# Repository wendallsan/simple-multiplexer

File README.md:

# SynthUx Academy Simple Board Multiplexer Daughterboard

This is a small PCB that is designed to fit on the perfboard section at the bottom right of the Simple Board from [SynthUX Academy](https://synthux.academy/simple). 

## Headers Explained

There are two headers on the board, one 2x8 header accepts all the analog inputs, while the 1x8 header provides connectivity to the Daisy Seed.  

### Analog Inputs Header
```
Pin   Mux IC  Channel
1	1   X0
2	1     X1
3	1     X2
4	1     X3
5	1     X4
6       1     X5
7	1     X6
8	1     X7
9	2     X0
10	2     X1
11	2     X2
12	2     X3
13	2     X4
14	2     X5
15	2     X6
16	2     X7
```

### Daisy Seed I/O Header
```
+ - positive voltage input-- connects  Pin 21 (AGND) of the Daisy Seed
A - Channel Select A
B - Channel Select B
C - Channel Select C
M1 - Mux 1 Out
M2 - Mux 2 Out
GND - ground -- connect to your Ground network (and Pins 20 and 40 on the Daisy Seed)
```  
Pin 7 on the I/O header is not used.  

## Bill of Materials  

```
2x CD4051 IC's in SOIC-16 format
2x 10nF capacitors in 0805 format
1x 2x8 female header with 2.54mm spacing
1x 1x8 female header with 2.54mm spacing  
4x single male pins for mounting the board
```

## Images

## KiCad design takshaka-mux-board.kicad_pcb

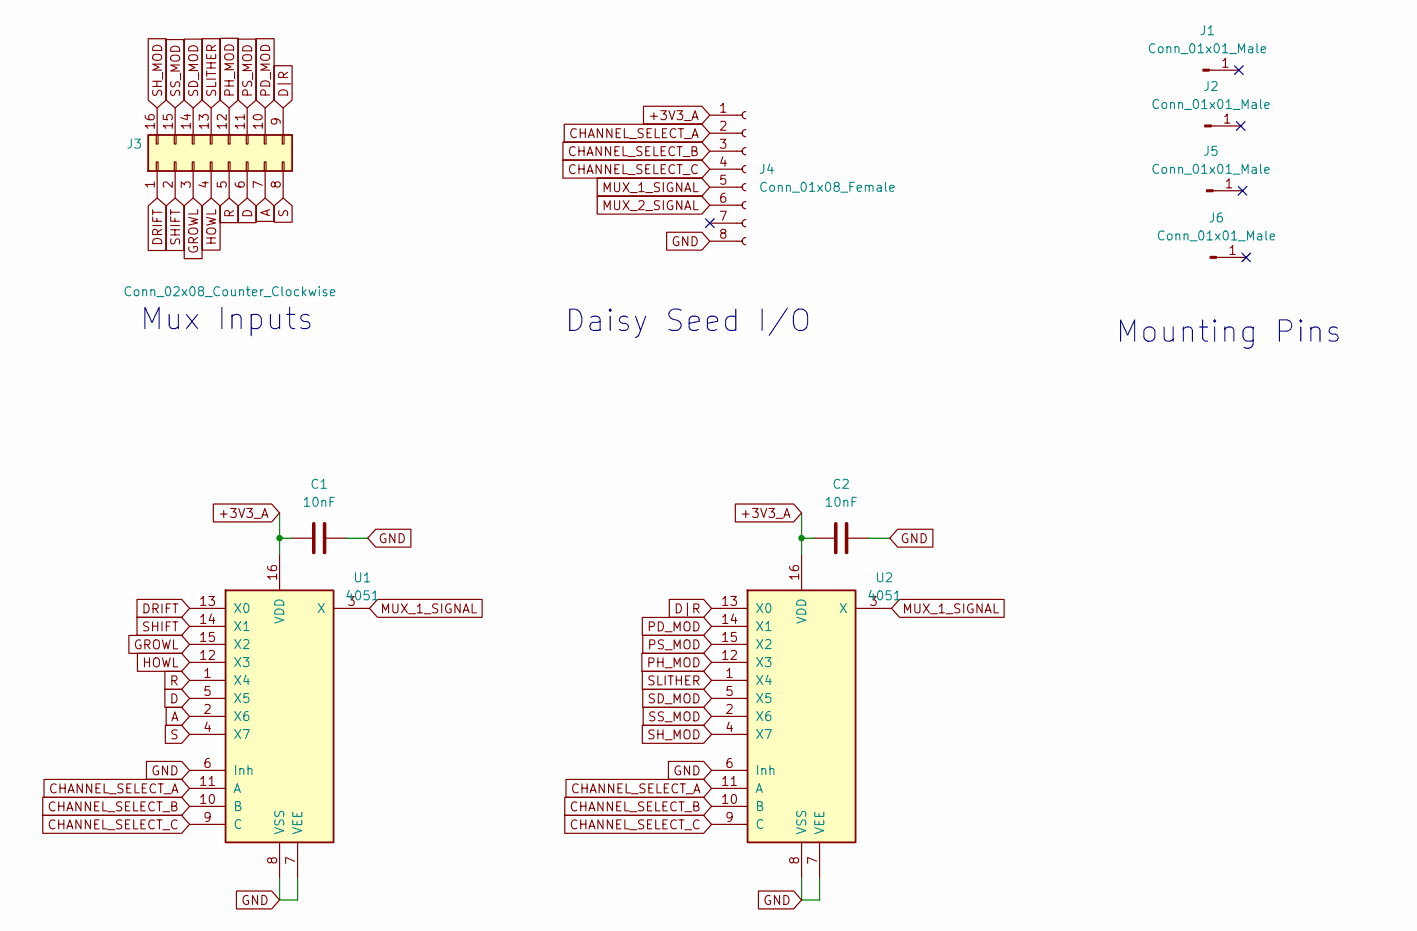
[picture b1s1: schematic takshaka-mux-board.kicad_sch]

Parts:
C1, C2: 10nF; C_0805_2012Metric
J1, J2, J5, J6: Conn_01x01_Male; PinHeader_1x01_P2.54mm_Vertical
J3: Conn_02x08_Counter_Clockwise; PinSocket_2x08_P2.54mm_Vertical
J4: Conn_01x08_Female; PinSocket_1x08_P2.54mm_Vertical
U1, U2: 4051; SOIC-16_3.9x9.9mm_P1.27mm

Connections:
+3V3_A: C1.1, C2.1, J4.1, U1.16 (VDD), U2.16 (VDD)
A: J3.7, U1.2 (X6)
CHANNEL_SELECT_A: J4.2, U1.11 (A), U2.11 (A)
CHANNEL_SELECT_B: J4.3, U1.10 (B), U2.10 (B)
CHANNEL_SELECT_C: J4.4, U1.9 (C), U2.9 (C)
D: J3.6, U1.5 (X5)
DRIFT: J3.1, U1.13 (X0)
D|R: J3.9, U2.13 (X0)
GND: C1.2, C2.2, J4.8, U1.6 (Inh), U1.7 (VEE), U1.8 (VSS), U2.6 (Inh), U2.7 (VEE), U2.8 (VSS)
GROWL: J3.3, U1.15 (X2)
HOWL: J3.4, U1.12 (X3)
MUX_1_SIGNAL: J4.5, U1.3 (X), U2.3 (X)
MUX_2_SIGNAL: J4.6
PD_MOD: J3.10, U2.14 (X1)
PH_MOD: J3.12, U2.12 (X3)
PS_MOD: J3.11, U2.15 (X2)
R: J3.5, U1.1 (X4)
S: J3.8, U1.4 (X7)
SD_MOD: J3.14, U2.5 (X5)
SHIFT: J3.2, U1.14 (X1)
SH_MOD: J3.16, U2.4 (X7)
SLITHER: J3.13, U2.1 (X4)
SS_MOD: J3.15, U2.2 (X6)

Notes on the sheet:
Daisy Seed I/O
Mux Inputs
Mounting Pins

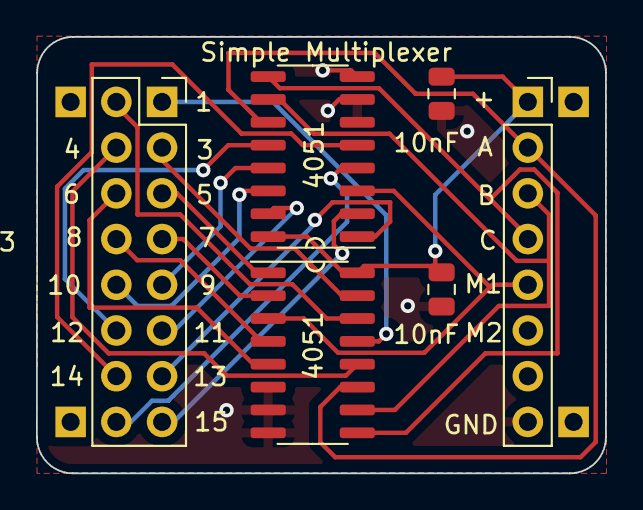
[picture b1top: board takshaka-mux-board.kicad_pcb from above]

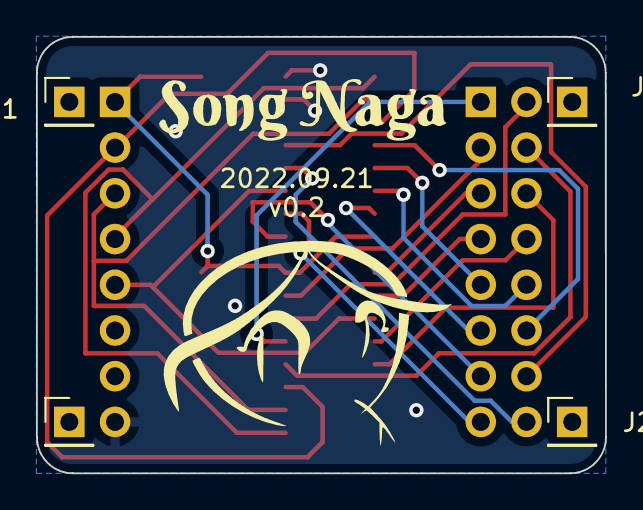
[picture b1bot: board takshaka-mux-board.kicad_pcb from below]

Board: 2 copper layers, 31.6 x 24.2 mm, 12 parts (6 on the bottom side), 22 nets.

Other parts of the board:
G1, G2: LOGO

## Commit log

2022-09-21 Initial commit.
2022-09-21 v0.2
2022-09-21 rebuilt gerbers files.
2022-09-21 added schematic PDF.
